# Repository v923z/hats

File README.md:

# Raspberry pi hats

1. [Hat One](https://github.com/v923z/hats/one)

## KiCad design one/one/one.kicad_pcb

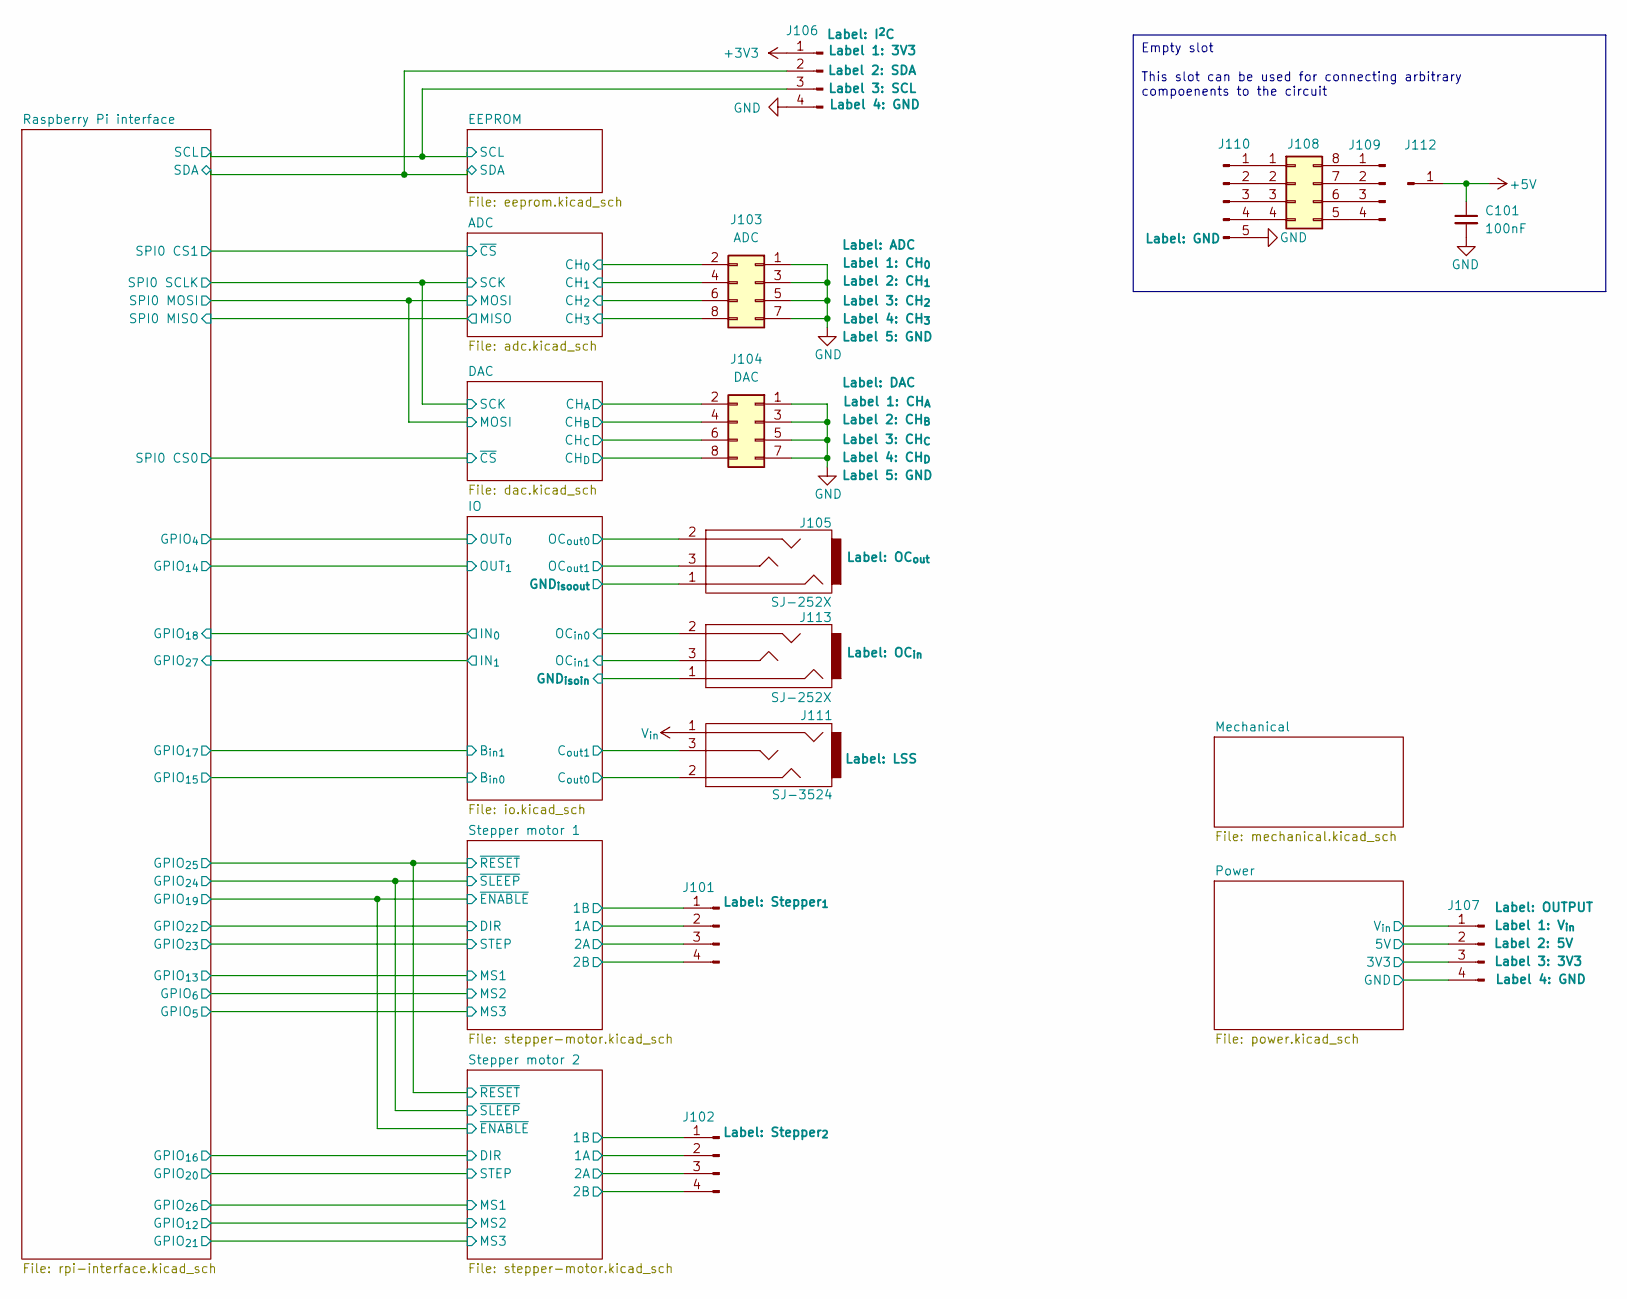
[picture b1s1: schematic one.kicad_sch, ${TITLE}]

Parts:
C101: 100nF; C_0603_1608Metric
J101, J102, J109: Conn_01x04_Pin; PinHeader_1x04_P2.54mm_Vertical
J103: ADC; PinHeader_2x04_P2.54mm_Vertical
J104: DAC; PinHeader_2x04_P2.54mm_Vertical
J105, J113: SJ-252X; MPN SJ-2523-SMT-TR
J106, J107: Conn_01x04_Pin; PinHeader_1x04_P2.54mm_Horizontal
J108: Conn_02x04_Counter_Clockwise; DIP-8_W7.62mm_Socket
J110: Conn_01x05_Pin; PinHeader_1x05_P2.54mm_Vertical
J111: SJ-3524; MPN SJ-3524-SMT-TR-PI
J112: Conn_01x01_Pin; PinHeader_1x01_P2.54mm_Vertical

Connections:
+3V3: J106.1, J107.3; also elsewhere on the board
+5V: C101.1, J107.2, J112.1; also elsewhere on the board
/ADC/CH_{0}: J103.2; also elsewhere on the board
/ADC/CH_{1}: J103.4; also elsewhere on the board
/ADC/CH_{2}: J103.6; also elsewhere on the board
/ADC/CH_{3}: J103.8; also elsewhere on the board
/DAC/CH_{A}: J104.2; also elsewhere on the board
/DAC/CH_{B}: J104.4; also elsewhere on the board
/DAC/CH_{C}: J104.6; also elsewhere on the board
/DAC/CH_{D}: J104.8; also elsewhere on the board
/EEPROM/SCL: J106.3; also elsewhere on the board
/EEPROM/SDA: J106.2; also elsewhere on the board
/IO/C_{out}_{0}: J111.2; also elsewhere on the board
/IO/C_{out}_{1}: J111.3; also elsewhere on the board
/IO/GND_{iso}_{in}: J113.1; also elsewhere on the board
/IO/GND_{iso}_{out}: J105.1; also elsewhere on the board
/IO/OC_{in}_{0}: J113.2; also elsewhere on the board
/IO/OC_{in}_{1}: J113.3; also elsewhere on the board
/IO/OC_{out}_{0}: J105.2; also elsewhere on the board
/IO/OC_{out}_{1}: J105.3; also elsewhere on the board
/Stepper motor 1/1A: J101.2; also elsewhere on the board
/Stepper motor 1/1B: J101.1; also elsewhere on the board
/Stepper motor 1/2A: J101.3; also elsewhere on the board
/Stepper motor 1/2B: J101.4; also elsewhere on the board
/Stepper motor 2/1A: J102.2; also elsewhere on the board
/Stepper motor 2/1B: J102.1; also elsewhere on the board
/Stepper motor 2/2A: J102.3; also elsewhere on the board
/Stepper motor 2/2B: J102.4; also elsewhere on the board
GND: C101.2, J103.1, J103.3, J103.5, J103.7, J104.1, J104.3, J104.5, J104.7, J106.4, J107.4, J110.5; also elsewhere on the board
unnamed: J108.1, J110.1
unnamed: J108.2, J110.2
unnamed: J108.3, J110.3
unnamed: J108.4, J110.4
unnamed: J108.5, J109.4
unnamed: J108.6, J109.3
unnamed: J108.7, J109.2
unnamed: J108.8, J109.1
V_{in}: J107.1, J111.1; also elsewhere on the board

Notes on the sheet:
Empty slot This slot can be used for connecting arbitrary compoenents to the circuit

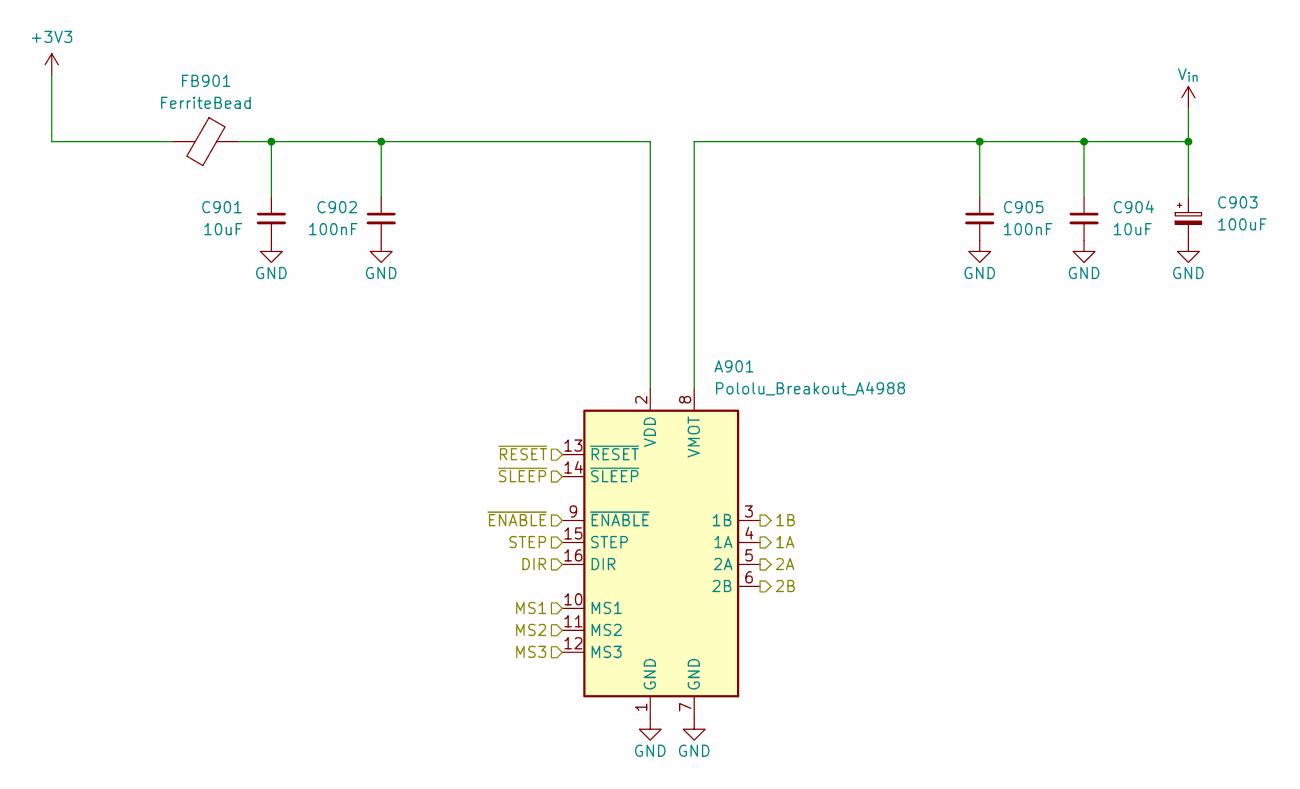
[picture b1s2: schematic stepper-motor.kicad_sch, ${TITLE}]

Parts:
A901: Pololu_Breakout_A4988; Pololu_Breakout-16_15.2x20.3mm
C901, C904: 10uF; C_0603_1608Metric
C902, C905: 100nF; C_0603_1608Metric
C903: 100uF; C_Elec_5x5.8
FB901: FerriteBead; L_0603_1608Metric

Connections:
+3V3: FB901.2; also elsewhere on the board
/Raspberry Pi interface/GPIO_{12}: A901.11 (MS2); also elsewhere on the board
/Raspberry Pi interface/GPIO_{16}: A901.16 (DIR); also elsewhere on the board
/Raspberry Pi interface/GPIO_{19}: A901.9 (~ENABLE); also elsewhere on the board
/Raspberry Pi interface/GPIO_{20}: A901.15 (STEP); also elsewhere on the board
/Raspberry Pi interface/GPIO_{21}: A901.12 (MS3); also elsewhere on the board
/Raspberry Pi interface/GPIO_{24}: A901.14 (~SLEEP); also elsewhere on the board
/Raspberry Pi interface/GPIO_{25}: A901.13 (~RESET); also elsewhere on the board
/Raspberry Pi interface/GPIO_{26}: A901.10 (MS1); also elsewhere on the board
/Stepper motor 2/1A: A901.4 (1A); also elsewhere on the board
/Stepper motor 2/1B: A901.3 (1B); also elsewhere on the board
/Stepper motor 2/2A: A901.5 (2A); also elsewhere on the board
/Stepper motor 2/2B: A901.6 (2B); also elsewhere on the board
GND: A901.1 (GND), A901.7 (GND), C901.2, C902.2, C903.2, C904.2, C905.2; also elsewhere on the board
unnamed: A901.2 (VDD), C901.1, C902.1, FB901.1
V_{in}: A901.8 (VMOT), C903.1, C904.1, C905.1; also elsewhere on the board

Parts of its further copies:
A701: Pololu_Breakout_A4988; Pololu_Breakout-16_15.2x20.3mm
C701, C704: 10uF; C_0603_1608Metric
C702, C705: 100nF; C_0603_1608Metric
C703: 100uF; C_Elec_5x5.8
FB701: FerriteBead; L_0603_1608Metric

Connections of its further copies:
+3V3: FB701.2; also elsewhere on the board
/Raspberry Pi interface/GPIO_{5}: A701.12 (MS3); also elsewhere on the board
/Raspberry Pi interface/GPIO_{6}: A701.11 (MS2); also elsewhere on the board
/Raspberry Pi interface/GPIO_{13}: A701.10 (MS1); also elsewhere on the board
/Raspberry Pi interface/GPIO_{19}: A701.9 (~ENABLE); also elsewhere on the board
/Raspberry Pi interface/GPIO_{22}: A701.16 (DIR); also elsewhere on the board
/Raspberry Pi interface/GPIO_{23}: A701.15 (STEP); also elsewhere on the board
/Raspberry Pi interface/GPIO_{24}: A701.14 (~SLEEP); also elsewhere on the board
/Raspberry Pi interface/GPIO_{25}: A701.13 (~RESET); also elsewhere on the board
/Stepper motor 1/1A: A701.4 (1A); also elsewhere on the board
/Stepper motor 1/1B: A701.3 (1B); also elsewhere on the board
/Stepper motor 1/2A: A701.5 (2A); also elsewhere on the board
/Stepper motor 1/2B: A701.6 (2B); also elsewhere on the board
GND: A701.1 (GND), A701.7 (GND), C701.2, C702.2, C703.2, C704.2, C705.2; also elsewhere on the board
unnamed: A701.2 (VDD), C701.1, C702.1, FB701.1
V_{in}: A701.8 (VMOT), C703.1, C704.1, C705.1; also elsewhere on the board

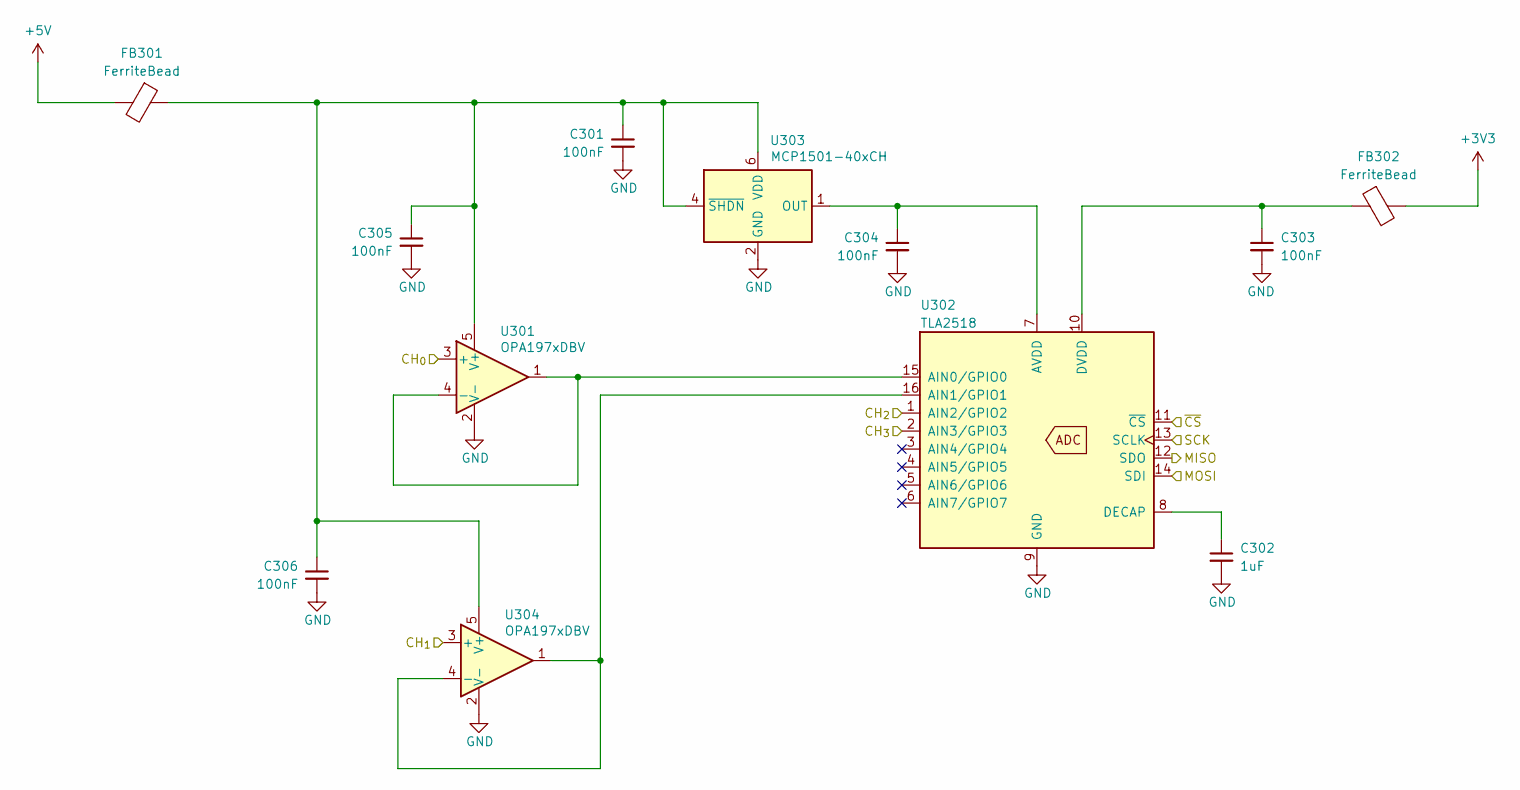
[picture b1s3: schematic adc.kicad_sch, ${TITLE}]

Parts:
C301, C303, C304, C305, C306: 100nF; C_0603_1608Metric
C302: 1uF; C_0603_1608Metric
FB301, FB302: FerriteBead; L_0603_1608Metric
U301, U304: OPA197xDBV; SOT-23-5; MPN OPA197IDBVR
U302: TLA2518; WQFN-16-1EP_3x3mm_P0.5mm_EP1.6x1.6mm; MPN TLA2518IRTER
U303: MCP1501-40xCH; SOT-23-6; MPN MCP1501T-40E/CHY

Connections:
+3V3: FB302.2; also elsewhere on the board
+5V: FB301.2; also elsewhere on the board
/ADC/CH_{0}: U301.3 (+); also elsewhere on the board
/ADC/CH_{1}: U304.3 (+); also elsewhere on the board
/ADC/CH_{2}: U302.1 (AIN2/GPIO2); also elsewhere on the board
/ADC/CH_{3}: U302.2 (AIN3/GPIO3); also elsewhere on the board
/ADC/MISO: U302.12 (SDO); also elsewhere on the board
/ADC/MOSI: U302.14 (SDI); also elsewhere on the board
/ADC/SCK: U302.13 (SCLK); also elsewhere on the board
/ADC/~CS: U302.11 (~CS); also elsewhere on the board
GND: C301.2, C302.2, C303.2, C304.2, C305.2, C306.2, U301.2 (V-), U302.9 (GND), U302.17 (GND), U303.2 (GND), U303.3 (GND), U303.5 (GND), U304.2 (V-); also elsewhere on the board
unnamed: U301.1, U301.4 (-), U302.15 (AIN0/GPIO0)
unnamed: C301.1, C305.1, C306.1, FB301.1, U301.5 (V+), U303.4 (~SHDN), U303.6 (VDD), U304.5 (V+)
unnamed: U302.16 (AIN1/GPIO1), U304.1, U304.4 (-)
unnamed: C304.1, U302.7 (AVDD), U303.1 (OUT)
unnamed: C302.1, U302.8 (DECAP)
unnamed: C303.1, FB302.1, U302.10 (DVDD)

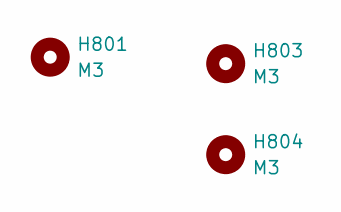
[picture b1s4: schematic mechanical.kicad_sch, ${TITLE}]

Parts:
H801, H803, H804: M3; MountingHole_3.2mm_M3_DIN965

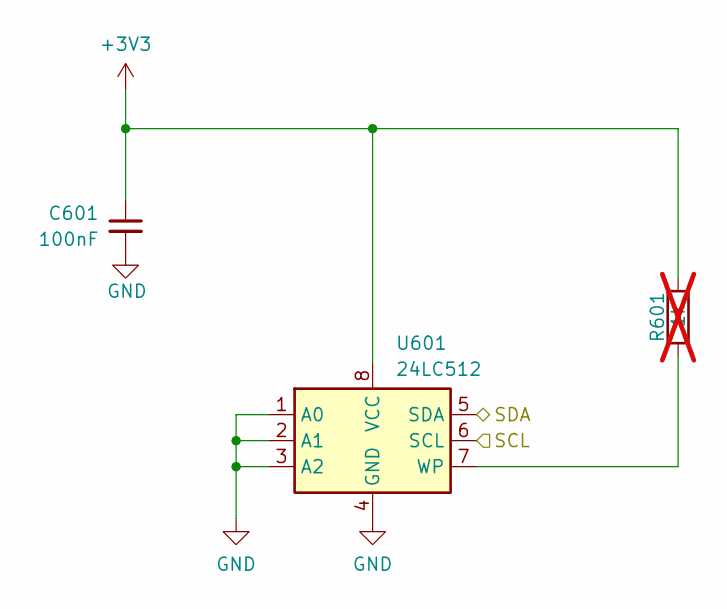
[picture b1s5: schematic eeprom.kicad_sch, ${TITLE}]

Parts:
C601: 100nF; C_0603_1608Metric
R601: 1k; R_0603_1608Metric; Tolerance 5%; not fitted
U601: 24LC512; DFN-8-1EP_3x2mm_P0.5mm_EP1.7x1.4mm; MPN M24512-DFMC6TG

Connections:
+3V3: C601.1, R601.2, U601.8 (VCC); also elsewhere on the board
/EEPROM/SCL: U601.6 (SCL); also elsewhere on the board
/EEPROM/SDA: U601.5 (SDA); also elsewhere on the board
GND: C601.2, U601.1 (A0), U601.2 (A1), U601.3 (A2), U601.4 (GND); also elsewhere on the board
unnamed: R601.1, U601.7 (WP)

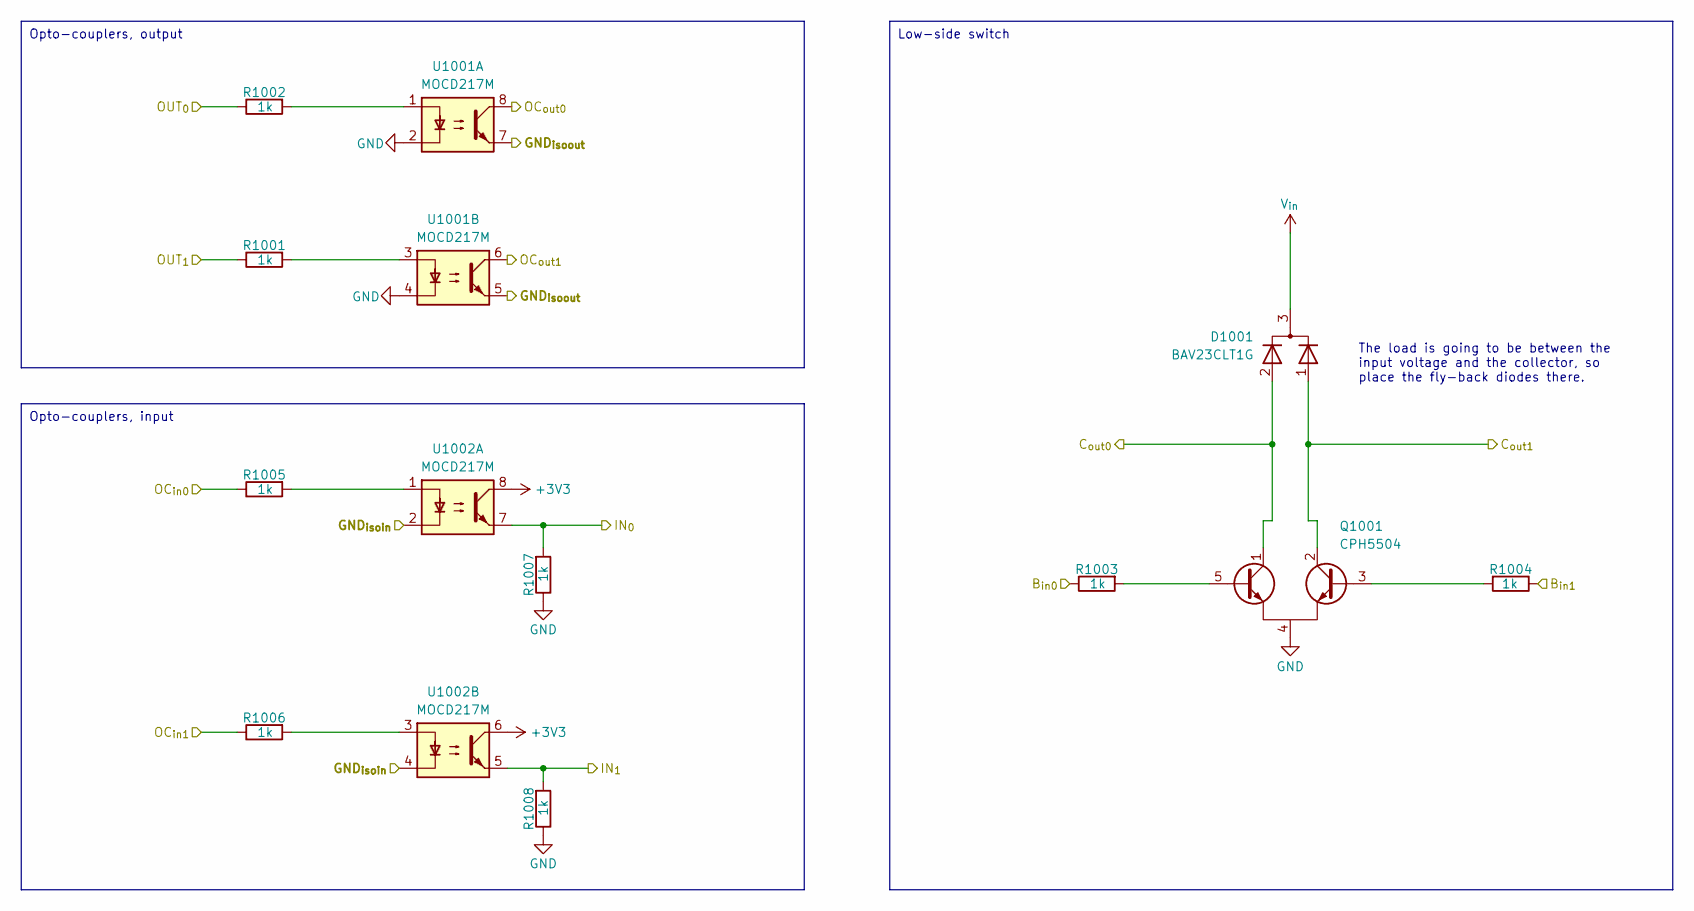
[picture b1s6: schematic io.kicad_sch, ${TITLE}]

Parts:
D1001: BAV23CLT1G; SOT-23-3; MPN BAV23CLT1G
Q1001: CPH5504; TSOT-23-5-mirrored; MPN CPH5504-TL-E
R1001, R1002, R1003, R1004, R1005, R1006, R1007, R1008: 1k; R_0603_1608Metric; Tolerance 5%
U1001, U1002: MOCD217M; SOIC-8_3.9x4.9mm_P1.27mm; MPN MOCD217R2M

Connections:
+3V3: U1002.6, U1002.8; also elsewhere on the board
/IO/B_{in}_{0}: R1003.1; also elsewhere on the board
/IO/B_{in}_{1}: R1004.1; also elsewhere on the board
/IO/C_{out}_{0}: D1001.2 (A), Q1001.1 (C1); also elsewhere on the board
/IO/C_{out}_{1}: D1001.1 (A), Q1001.2 (C2); also elsewhere on the board
/IO/GND_{iso}_{in}: U1002.2, U1002.4; also elsewhere on the board
/IO/GND_{iso}_{out}: U1001.5, U1001.7; also elsewhere on the board
/IO/IN_{0}: R1007.2, U1002.7; also elsewhere on the board
/IO/IN_{1}: R1008.2, U1002.5; also elsewhere on the board
/IO/OC_{in}_{0}: R1005.1; also elsewhere on the board
/IO/OC_{in}_{1}: R1006.1; also elsewhere on the board
/IO/OC_{out}_{0}: U1001.8; also elsewhere on the board
/IO/OC_{out}_{1}: U1001.6; also elsewhere on the board
/IO/OUT_{0}: R1002.1; also elsewhere on the board
/IO/OUT_{1}: R1001.1; also elsewhere on the board
GND: Q1001.4 (E), R1007.1, R1008.1, U1001.2, U1001.4; also elsewhere on the board
unnamed: Q1001.5 (B1), R1003.2
unnamed: Q1001.3 (B2), R1004.2
unnamed: R1001.2, U1001.3
unnamed: R1002.2, U1001.1
unnamed: R1005.2, U1002.1
unnamed: R1006.2, U1002.3
V_{in}: D1001.3 (K); also elsewhere on the board

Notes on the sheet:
Opto-couplers, input
Opto-couplers, output
Low-side switch
The load is going to be between the input voltage and the collector, so place the fly-back diodes there.

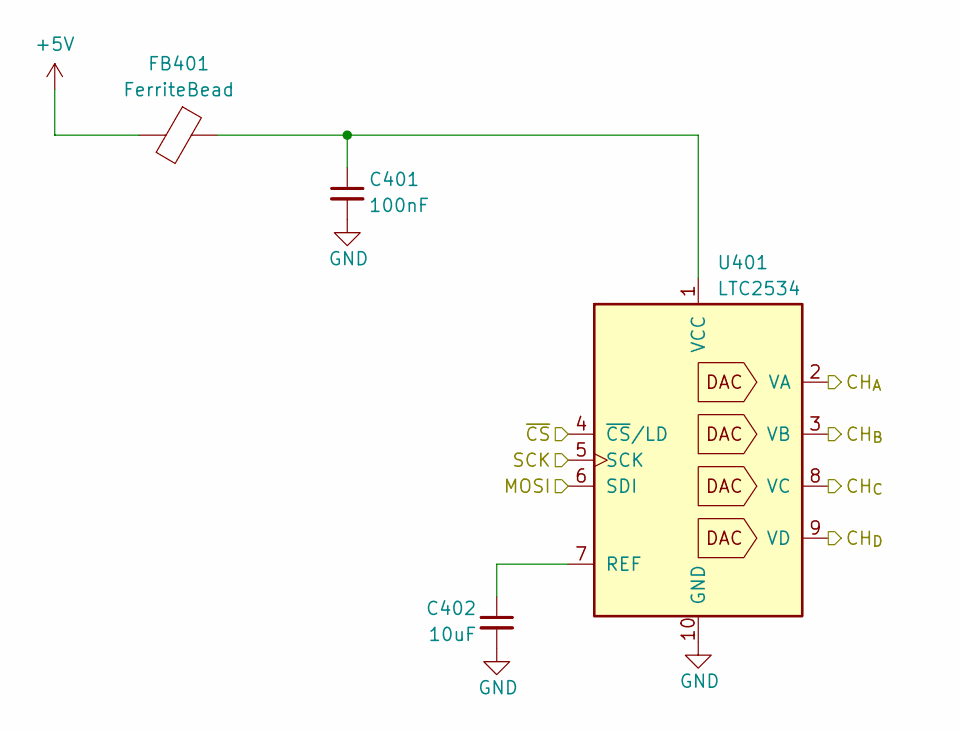
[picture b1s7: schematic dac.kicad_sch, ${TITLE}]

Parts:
C401: 100nF; C_0603_1608Metric
C402: 10uF; C_0603_1608Metric
FB401: FerriteBead; L_0603_1608Metric
U401: LTC2534; MSOP-10-1EP_3x3mm_P0.5mm_EP1.68x1.88mm; MPN LTC2634CMSE-LZ12#PBF

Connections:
+5V: FB401.2; also elsewhere on the board
/ADC/MOSI: U401.6 (SDI); also elsewhere on the board
/ADC/SCK: U401.5 (SCK); also elsewhere on the board
/DAC/CH_{A}: U401.2 (VA); also elsewhere on the board
/DAC/CH_{B}: U401.3 (VB); also elsewhere on the board
/DAC/CH_{C}: U401.8 (VC); also elsewhere on the board
/DAC/CH_{D}: U401.9 (VD); also elsewhere on the board
/DAC/~CS: U401.4 (~CS/LD); also elsewhere on the board
GND: C401.2, C402.2, U401.10 (GND), U401.11 (GND); also elsewhere on the board
unnamed: C402.1, U401.7 (REF)
unnamed: C401.1, FB401.1, U401.1 (VCC)

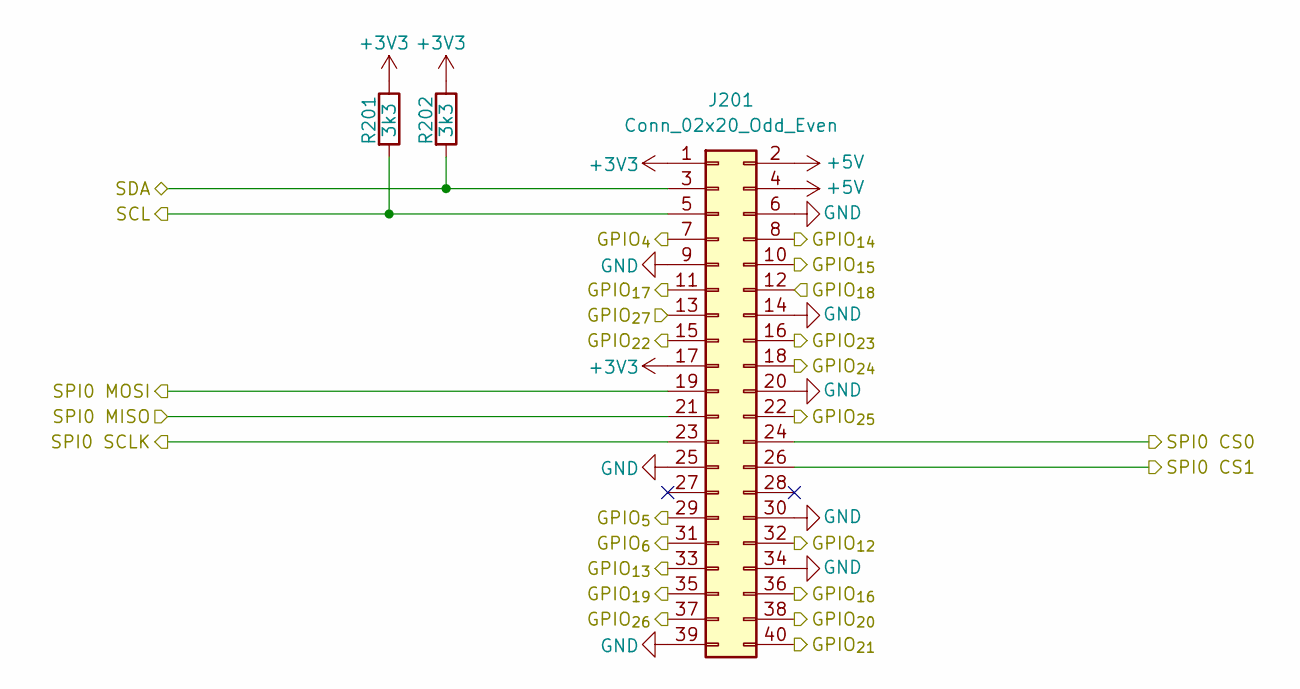
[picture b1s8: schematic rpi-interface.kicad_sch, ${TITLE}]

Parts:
J201: Conn_02x20_Odd_Even; PinSocket_2x20_P2.54mm_Vertical_SMD
R201, R202: 3k3; R_0603_1608Metric; Tolerance 5%

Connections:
+3V3: J201.1, J201.17, R201.1, R202.1; also elsewhere on the board
+5V: J201.2, J201.4; also elsewhere on the board
/ADC/MISO: J201.21; also elsewhere on the board
/ADC/MOSI: J201.19; also elsewhere on the board
/ADC/SCK: J201.23; also elsewhere on the board
/ADC/~CS: J201.26; also elsewhere on the board
/DAC/~CS: J201.24; also elsewhere on the board
/EEPROM/SCL: J201.5, R201.2; also elsewhere on the board
/EEPROM/SDA: J201.3, R202.2; also elsewhere on the board
/IO/B_{in}_{0}: J201.10; also elsewhere on the board
/IO/B_{in}_{1}: J201.11; also elsewhere on the board
/IO/IN_{0}: J201.12; also elsewhere on the board
/IO/IN_{1}: J201.13; also elsewhere on the board
/IO/OUT_{0}: J201.7; also elsewhere on the board
/IO/OUT_{1}: J201.8; also elsewhere on the board
/Raspberry Pi interface/GPIO_{5}: J201.29; also elsewhere on the board
/Raspberry Pi interface/GPIO_{6}: J201.31; also elsewhere on the board
/Raspberry Pi interface/GPIO_{12}: J201.32; also elsewhere on the board
/Raspberry Pi interface/GPIO_{13}: J201.33; also elsewhere on the board
/Raspberry Pi interface/GPIO_{16}: J201.36; also elsewhere on the board
/Raspberry Pi interface/GPIO_{19}: J201.35; also elsewhere on the board
/Raspberry Pi interface/GPIO_{20}: J201.38; also elsewhere on the board
/Raspberry Pi interface/GPIO_{21}: J201.40; also elsewhere on the board
/Raspberry Pi interface/GPIO_{22}: J201.15; also elsewhere on the board
/Raspberry Pi interface/GPIO_{23}: J201.16; also elsewhere on the board
/Raspberry Pi interface/GPIO_{24}: J201.18; also elsewhere on the board
/Raspberry Pi interface/GPIO_{25}: J201.22; also elsewhere on the board
/Raspberry Pi interface/GPIO_{26}: J201.37; also elsewhere on the board
GND: J201.6, J201.9, J201.14, J201.20, J201.25, J201.30, J201.34, J201.39; also elsewhere on the board

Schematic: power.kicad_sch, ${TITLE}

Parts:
C501: 10uF; C_0603_1608Metric
C502: 100nF; C_0603_1608Metric
C503: 100uF; C_Elec_5x5.8
J501: 12V; CUI-PJ-018; MPN PJ-018

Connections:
GND: C501.2, C502.2, C503.2, J501.2, J501.MP (MountPin); also elsewhere on the board
V_{in}: C501.1, C502.1, C503.1, J501.1; also elsewhere on the board

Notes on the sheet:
These potentials are broken out through a pin header. See the root page!

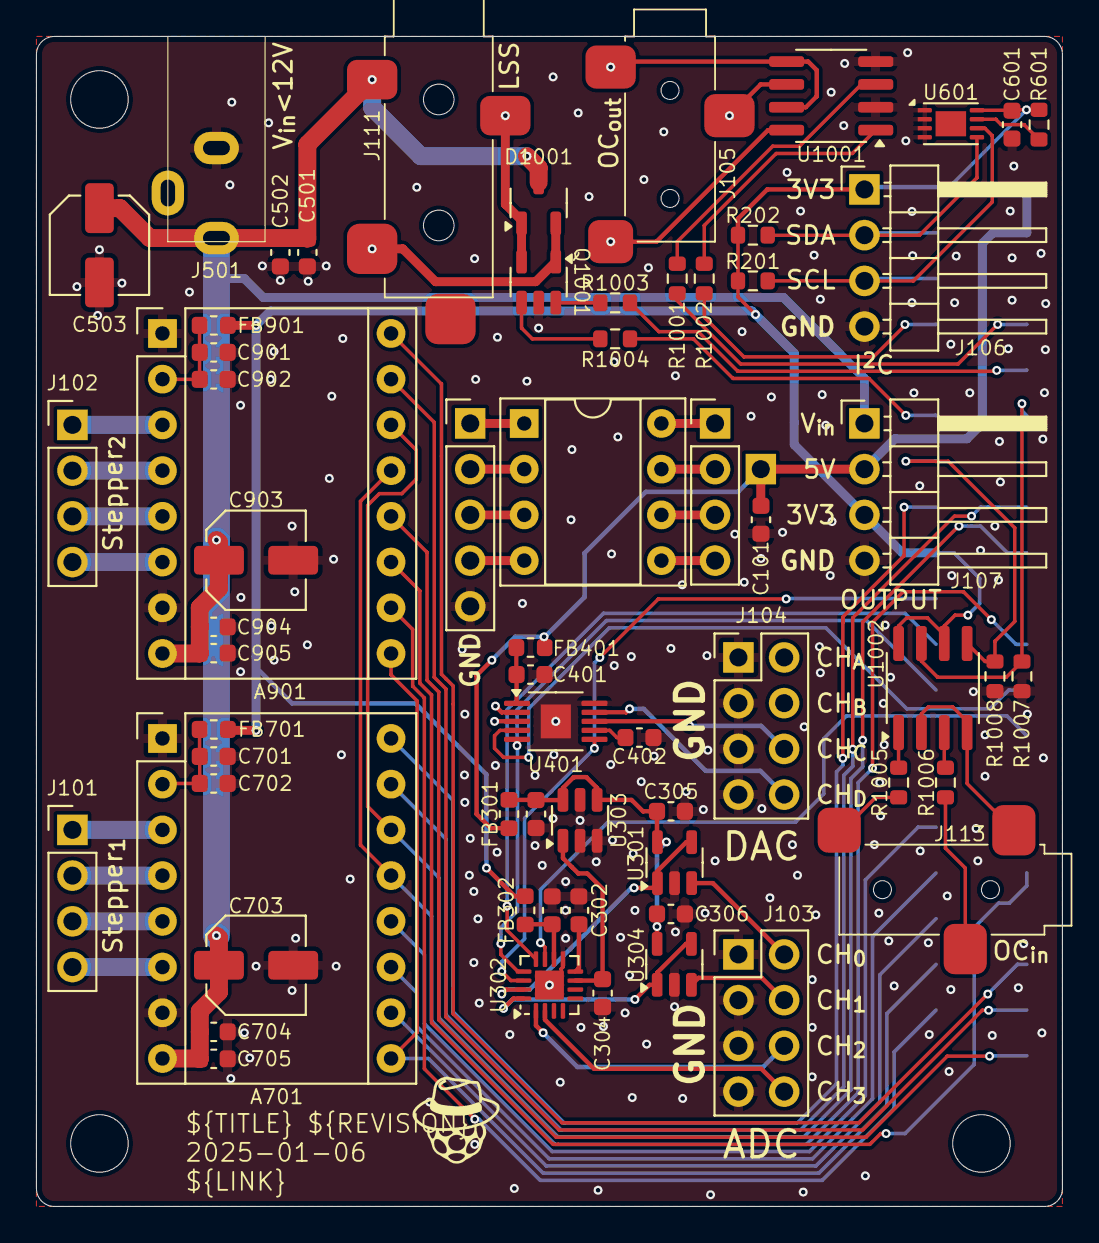
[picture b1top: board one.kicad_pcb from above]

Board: 4 copper layers, 57.0 x 65.0 mm, 69 parts (1 on the bottom side), 79 nets.

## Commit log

2025-01-05 add license file
2025-01-05 add README
2025-01-05 add schematics and layout
2025-01-05 add footprints
2025-01-05 move logo
2025-01-06 add EEPROM, remove one mounting hole
2025-01-26 add vendor links
